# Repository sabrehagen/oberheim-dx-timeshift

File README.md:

# DX TimeShift: a snare delay knob for the Oberheim DX

DX TimeShift adds one new knob to the rear panel of an Oberheim DX drum machine (1983), next to
the existing SNARE tuning pot. The knob makes the snare drum play later than the sequencer asks,
by anything from nothing at all up to one whole beat. This lets you "lay the snare back" behind the
groove. The delay is measured in beats, not milliseconds, so it stays musically the same when you
change the tempo. With the knob turned fully down the DX behaves exactly as it did from the factory.
The mod is a small plug-in circuit board. It sits in the socket of one chip on the DX main board
(U701), so it can be removed again. The only permanent change is one hole in the rear panel.

*The assembled DX TimeShift rev A board (3D render from the KiCad design). The 16-way box header
J1 DX PLUG is at the back right, the Arduino Nano at the front left, and the socket U1 for the
DX's own U701 chip is between them.*

> **Status: Design complete; NOT yet bench-verified on a real DX.**
>
> The circuit, the circuit board, the firmware and the drawings are finished and checked against
> each other. Nobody has yet fitted a TimeShift board to a real DX. Several facts about the DX were
> worked out from schematics, photos and the original firmware, and still need one measurement on
> the bench. The most important open questions are:
>
> 1. **Q0:** Is your unit a plain DX (main board 1721A)? The board does NOT fit a DXa (board 1906).
>    **Owner's answer (2026-11-06): yes, it is a plain Oberheim DX.** The technician still reads the
>    board title and the ROM labels when the lid is open, to record the board number and firmware version.
> 2. **Q1:** Is U701 in a socket? If it is soldered in, the mod is no longer fully reversible.
>    **Owner's note:** the voice chips on this unit were socketed after purchase. U701 is a logic chip,
>    not a voice chip, so the technician still checks it with a torch (one minute).
> 3. **Q2:** What do the snare trigger lines (RST2, FFA2, FFB2) really look like on a logic analyser?
> 4. **Q3:** Is there enough height under the closed lid for the board (about 32 mm)?
> 5. **Q4:** Does the U701 clock line (GEN0*) stay clean when it runs through the ribbon cable?
> 6. **Q5:** Does the CLOCK OUT tap at R791 behave as expected, and does it keep ticking when the sequencer is stopped?
> 7. **Q6:** Is there room behind the rear panel for the new pot?
> 8. **Q7:** Does the DX +5 V supply stay healthy with the board running?
> 9. **Ribbon mapping:** every one of the 16 conductors must pass a continuity check before first power-up.
>
> Each question, with the exact measurement that answers it, is in
> [docs/05-bench-verification.md](docs/05-bench-verification.md).

## Who this is for

* **The owner** of an Oberheim DX who wants a "laid back" snare. Read
  [docs/00-start-here.md](docs/00-start-here.md). It explains what the mod does, what it costs and
  how it will behave.
* **The electronics technician** who builds and fits it. You need to be comfortable with
  through-hole soldering, a multimeter, and working inside mains-powered vintage equipment. An
  oscilloscope or a logic analyser is needed for the verification steps. No surface-mount
  soldering is needed.
* **Anyone curious** about how a 1983 drum machine triggers its sounds. Read
  [docs/01-theory-of-operation.md](docs/01-theory-of-operation.md).

## If you are the technician, read in this order

| Step | Document | What you get from it |
|---|---|---|
| 1 | [docs/00-start-here.md](docs/00-start-here.md) | The big picture, the model check, the shopping list, the order of work |
| 2 | [docs/05-bench-verification.md](docs/05-bench-verification.md) | The open questions. Answer Q0, Q1, Q3 and Q6 before you order anything. |
| 3 | [docs/01-theory-of-operation.md](docs/01-theory-of-operation.md) | How the DX triggers the snare and how the TimeShift board delays it |
| 4 | [docs/bom.md](docs/bom.md) | Parts, part numbers, prices and tools |
| 5 | [docs/02-build-the-board.md](docs/02-build-the-board.md) | Ordering the PCB, soldering, making the ribbon cable, continuity check, flashing, bench test |
| 6 | [docs/03-install-in-the-dx.md](docs/03-install-in-the-dx.md) | Fitting the board, drilling the panel, the pot and clock wiring |
| 7 | [docs/04-test-and-calibrate.md](docs/04-test-and-calibrate.md) | First power-on, measurements, troubleshooting, how to remove the mod |
| Reference | [hardware/README.md](hardware/README.md) | The complete pin and net table. This is the reference for every pin number. |
| Reference | [firmware/README.md](firmware/README.md) | Flashing the Nano, settings, the serial status line |
| Reference | [hardware/mechanical/README.md](hardware/mechanical/README.md) | Drill template, wiring diagram, continuity sheet |

## Option B: a delayed snare EPROM (idea recorded, not yet documented)

A lighter alternative that needs no new circuit board: burn a copy of the snare sample EPROM
(U206, a socketed 2764) with a block of silence in front, so the snare plays late by a fixed
number of milliseconds. The tuning pot keeps working (the lag shrinks slightly when the snare is
tuned up). Limits: the lag is fixed, not tempo-locked, and the chip has room for roughly 20 to
60 ms of lead-in before the snare tail is cut (about 200 ms if the SJ2/SJ3 solder jumpers are
moved). A 27C256 on a small adapter with a two-pole switch could offer four selectable lags.
The script, procedure and adapter drawing for this option have not been written yet.
**To resume this work, start from [docs/NEXT-STEPS.md](docs/NEXT-STEPS.md), which holds the full brief.**

## Interactive 3D walkthrough

There is an interactive 3D walkthrough of the DX, the board, the build and the installation.
It is live at
**<https://jacksondelahunt.com/oberheim-dx-timeshift/>** (also reachable as
<https://sabrehagen.github.io/oberheim-dx-timeshift/>). It plays at 2x by default. The DX is drawn by a
procedural model built from the reference photos (v2, no third-party assets). The earlier simple
stylised model is still available with the **DX model** button in the header or by adding
`?dx=v1` to the address. To run it on your own computer, see
[webapp/README.md](webapp/README.md).

*The web walkthrough. Each stage has a 3D view with labels on the real parts and a side panel
with the text. Items that are TO BE CONFIRMED are marked in amber.*

## Repository map

| Folder or file | What is in it |
|---|---|
| `README.md` | This page |
| `PROJECT_BRIEF.md` | The design brief: the single source of truth for the design decisions (sections 3 to 3.6) |
| `docs/` | The step-by-step guides (00 to 05), the bill of materials, the research findings and the collected reference documents |
| `hardware/` | The KiCad 9 design, Gerber files for ordering the PCB, schematic PDF, 3D renders and the mechanical drawings |
| `firmware/` | The Arduino Nano program, its settings file and PC tests |
| `webapp/` | The interactive 3D walkthrough (Vite and three.js) |
| `.github/` | The workflow that publishes the walkthrough to GitHub Pages |

## Safety notes

* **Mains voltage.** The DX has a mains transformer, fuse and line filter inside the case. Always
  switch off and **unplug the mains cable** before you open the lid or touch anything inside.
* **Stored energy.** The DX power supply has a 10 000 µF capacitor (C723). Wait at least a minute
  after unplugging before you work inside.
* **Static.** U701 is a 1983 CMOS chip (Motorola MC14174B). Wear an anti-static wrist strap
  connected to the DX chassis while you handle it. It cannot be bought new in the same form.
* **The memory battery.** The DX keeps your patterns in battery-backed memory. Never connect
  anything to the battery-backed "+5M" rail. Do not remove the battery or the memory chips. Save
  your patterns to cassette before you start, as the warning printed on the DX board advises.
* **USB.** The Nano's 5 V pin is connected to the DX logic supply. **Unplug the Nano before you
  connect USB**, or connect USB only while the DX is switched ON. Never plug USB into the Nano
  while it sits in an installed board in a switched-off DX.
* **Do not force anything.** Old sockets and chip legs bend easily. If a part does not go in,
  stop and look.

## Licence and credits

* The project's own original work is licensed as set out in [LICENSE.md](LICENSE.md): the
  hardware design under **CERN-OHL-P v2**, and the firmware, web app and documentation under
  **MIT**. The owner may change this later.
* The documents, schematics, manuals and photos in `docs/reference/` belong to their owners
  (Oberheim Electronics or its successors, Electrongate, the E&MM publisher, and the Wikimedia
  Commons photographers under their stated licences). They are kept here for repair and
  modification research only. See [docs/reference/INDEX.md](docs/reference/INDEX.md) for each
  source and its copyright notice.
* The research behind every pin number and timing value is in
  [docs/research/dx-findings.md](docs/research/dx-findings.md), with citations.

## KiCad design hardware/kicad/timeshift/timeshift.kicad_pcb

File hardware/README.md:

# DX TimeShift rev A: hardware

This folder holds the complete KiCad 9 design of the DX TimeShift board (snare delay
interposer for the Oberheim DX, board 1721A, socket U701). It also holds every file made
from that design. The circuit is exactly PROJECT_BRIEF.md section 3.5 (LOCKED). The signal
facts behind it are in `docs/research/dx-findings.md` sections b, c, d and h.

> **Fits Oberheim DX board 1721A (U701). NOT for the DXa (board 1906, U715).**
> **UNPLUG NANO BEFORE USB.** The Nano's 5 V pin is wired to the DX logic rail. Flash the Nano
> while it is OUT of the board, or only while the DX is switched on.

## 1. What each file is

| Path | What it is |
|---|---|
| `kicad/timeshift/timeshift.kicad_pro` | KiCad 9 project. Open this file in KiCad. |
| `kicad/timeshift/timeshift.kicad_sch` | Schematic, one A3 sheet in blocks A to F. Every library symbol is embedded. |
| `kicad/timeshift/timeshift.kicad_pcb` | PCB: 2 layers, fully routed, GND pours on both layers |
| `kicad/timeshift/timeshift.kicad_sym`, `sym-lib-table` | Project symbol library. It has one symbol, J1 `DX_PLUG_2x08`. |
| `kicad/timeshift/timeshift.pretty/Arduino_Nano_Socketed.kicad_mod`, `fp-lib-table` | Project footprint: `Module:Arduino_Nano` with identical pads, plus 3D models of the Nano and its two 1x15 female headers |
| `kicad/timeshift/3d/Arduino_Nano_v3_on_sockets.step` | Simple colour 3D model of a Nano v3 on sockets. The KiCad library has no Nano model. |
| `kicad/timeshift/reports/erc.rpt` | ERC report: **0 errors, 0 warnings** (all severities) |
| `kicad/timeshift/reports/drc.rpt` | DRC report, including schematic parity: **0 violations, 0 unconnected, 0 parity issues** (all severities) |
| `kicad/timeshift/reports/timeshift.net` | Netlist exported from the schematic. The PCB is built from it. |
| `kicad/tools/` | Generator scripts. The whole design is rebuilt from `netlist.py` (section 3). |
| `kicad/3dmodels-cache/` | The KiCad 9 library 3D models this board uses (3.7 MB). **Committed to the repo**, so renders, GLB and STEP rebuild offline. `fetch_3dmodels.sh` re-downloads any that are missing. |
| `exports/schematic.pdf`, `exports/schematic.svg` | Schematic for printing or viewing |
| `exports/pcb-top.svg`, `exports/pcb-bottom.svg` | Copper + mask + silkscreen + outline, top and bottom (the bottom view is mirrored) |
| `exports/fab-assembly-top.pdf` | Fab/assembly drawing: F.Fab + F.Silkscreen + Edge.Cuts with title block |
| `exports/board.glb` | 3D model with tracks, pads, zones, silkscreen, soldermask and component models. It is used by the web app. |
| `exports/board.step` | 3D STEP of the assembled board, for mechanical CAD |
| `exports/bom.csv` | BOM exported from the schematic, grouped by value and footprint, with part numbers. The J1 cable row names the DIP-16 IDC plug as **Adam Tech FDP-316-T** (alternative HARTING 09181169622), the same part as `docs/bom.csv`. |
| `exports/positions.csv` | Component positions (mm, KiCad coordinates, top side) |
| `gerbers/timeshift-revA-gerbers.zip` | **Upload this to JLCPCB/PCBWay.** See `gerbers/README.md` for order settings. |
| `renders/top.png`, `bottom.png`, `perspective.png`, `perspective-2.png` | 3D renders, 2384 x 1680 px, high quality |
| `renders/top-bare-board.png` | Top render without parts, so all the silkscreen is visible |
| `renders/assembly-diagram.svg` / `.png` | **Labelled top view for assembly.** Every connector, IC and test point has a callout. |

## 2. The board at a glance

* 84.0 x 63.0 mm, 2 layers, FR-4 1.6 mm, all parts through-hole, 4 x M3 (3.2 mm) mounting
  holes 3.5 mm in from each corner (hole centres 77.0 x 56.0 mm apart).
* Tracks are 0.5 mm for signals and 0.8 mm for +5V. Clearance is 0.2 mm. Vias are 1.0/0.5 mm.
  Copper is kept 0.5 mm from the board edge.
* GND is carried by a copper pour on the **bottom** (the main plane, as the brief asks). A
  second GND pour on the top joins the bottom islands that the tracks cut off. Every GND pad
  has at least two thermal spokes or a solid connection.
* Layout (top view): J1 "DX PLUG" is top centre, with U1 (socket for the original U701)
  directly below it. U3 (74HC157) is on the left and the 1 k resistors R1 to R3 sit between
  U3 and U1. The Nano is across the bottom with its USB end on the LEFT. U4 (74HC14) is
  bottom right. **All three DIP sockets (U1, U3, U4) have their notch / pin 1 at the LEFT
  end.** J3 "CLK" and J2 "POT" are on the right edge. The PPQN jumper JP1 is at the left
  edge. Test points TP2/TP3/TP4 are next to J1, TP1 is at the left edge and TP5 is next to
  U4.
* Decoupling sits at the pins it serves. C2 is about 3 mm from U1 pin 16 and C3 about 6 mm
  from U3 pin 16. C4's +5V pad is 4.0 mm from U4 pin 14 (VCC). C5 is just below the Nano:
  its +5V pad is 3.2 mm from Nano pin 27 (+5V) and its GND pad 3.2 mm from pin 29 (GND).

## 3. How to open and how to regenerate

**Open:** install KiCad 9 and open `kicad/timeshift/timeshift.kicad_pro`. The project
libraries (`timeshift.kicad_sym`, `timeshift.pretty`) are found through `${KIPRJMOD}`. All
other symbols and footprints come from the standard KiCad 9 libraries.

**Regenerate everything** with Docker. This rebuilds the libraries, schematic, ERC, netlist
check, PCB, autorouting, pours, DRC, all exports, Gerbers, renders and the diagram:

```sh
docker pull kicad/kicad:9.0
docker pull ghcr.io/freerouting/freerouting:latest
hardware/kicad/tools/build_all.sh            # about 8 minutes, mostly the 3D renders
```

The 3D models come from the committed `hardware/kicad/3dmodels-cache/` (3.7 MB).
`build_all.sh` only downloads models that are missing there, so the build needs no network
access for them. It does need the two Docker images.

If Docker cannot bind-mount your checkout (for example, you are working inside a container),
start a helper container once and use copy mode. Copy mode only syncs `hardware/kicad`,
`exports`, `gerbers` and `renders`:

```sh
docker run -d --name kicadws kicad/kicad:9.0 sleep infinity
KX_MODE=copy hardware/kicad/tools/build_all.sh
```

Single steps, run from the repository root (this is what `tools/kx.sh` does):

```sh
K='docker run --rm --user '"$(id -u):$(id -g)"' -e HOME=/tmp -e KICAD9_3DMODEL_DIR=/work/hardware/kicad/3dmodels-cache -v '"$PWD"':/work -w /work kicad/kicad:9.0'
$K kicad-cli sch erc --severity-all -o hardware/kicad/timeshift/reports/erc.rpt hardware/kicad/timeshift/timeshift.kicad_sch
$K kicad-cli pcb drc --schematic-parity --severity-all -o hardware/kicad/timeshift/reports/drc.rpt hardware/kicad/timeshift/timeshift.kicad_pcb
$K kicad-cli sch export pdf -o hardware/exports/schematic.pdf hardware/kicad/timeshift/timeshift.kicad_sch
$K kicad-cli pcb export glb -f --subst-models --include-tracks --include-pads --include-zones --include-silkscreen --include-soldermask -o hardware/exports/board.glb hardware/kicad/timeshift/timeshift.kicad_pcb
$K kicad-cli pcb render --quality high --side top -w 2400 -h 1700 -o hardware/renders/top.png hardware/kicad/timeshift/timeshift.kicad_pcb
$K python3 hardware/kicad/tools/gen_pcb.py      # pcbnew Python API is available in the image
```

### The generator scripts (`kicad/tools/`)

| Script | Job |
|---|---|
| `netlist.py` | **Single source of truth:** every part, value, footprint, part number and pin-to-net assignment (= brief 3.5). The header-to-DIP mapping `HDR2DIP` is here. |
| `gen_libs.py` | Writes the J1 symbol (pin number = header pin, pin name = DIP pin), the socketed Nano footprint and the lib tables |
| `gen_project.py` | Writes `timeshift.kicad_pro`: net classes (Default 0.5 mm, Power 0.8 mm) and design rules |
| `gen_schematic.py` | Draws the schematic from `netlist.py`, using KiCad standard symbols embedded in the file |
| `check_netlist.py` | Compares the netlist KiCad exports from the schematic with `netlist.py`, net by net. The build stops on any difference. |
| `gen_pcb.py` + `silk.py` | Places the footprints and assigns nets from the exported netlist, so the PCB links to the schematic like "Update PCB from Schematic". Then it adds the outline and silkscreen and writes the Specctra DSN. |
| `route.sh` | Autoroutes with Freerouting in Docker. Neck-down is off, so every track keeps its class width. Freerouting is not fully deterministic, so the script retries (up to 5 runs) until 0 connections are unrouted. |
| `finish_pcb.py` | Imports the routes and adds and fills the GND pours. It gives a pad a solid zone connection where only one thermal spoke would fit. |
| `exports.sh` | All `kicad-cli` exports, Gerbers + drill files + zip, and 3D renders |
| `gen_diagram.py` | Draws the labelled assembly diagram from the real board data |
| `make_nano_3d.py` | Builds the Nano 3D model with CadQuery. It runs on the host and is optional, because the STEP file is committed. |
| `fetch_3dmodels.sh` | Downloads the KiCad 9 library 3D models this board uses (the Docker image ships without them) |
| `preview.py`, `bare_board.py` | Debug preview SVG and a model-less copy of the board for the bare-board render |

## 4. Design decisions

1. **Netlist first.** `netlist.py` is written straight from brief 3.5. The schematic is drawn
   from it, and KiCad's exported netlist must match it exactly (`check_netlist.py`). The PCB
   then takes its nets from that exported netlist, and DRC schematic parity confirms the PCB
   matches the schematic. So the brief, the schematic and the PCB cannot drift apart.
2. **J1 uses DIP pin numbers.** J1's symbol pin *numbers* are the box-header pins, which are
   also the ribbon conductors. Its pin *names* are `DIP1`...`DIP16`, the DIP-16 plug pin each
   header pin lands on. The symbol is drawn in DIP order, so it reads like U701. Net names say
   which U701 pin they carry (`U701_9_~{GEN0}`, `RST2_PLUG` = DIP 15, ...). The silkscreen
   also prints the DIP pin number next to every header pin ("DIP 16 15 ... 9" above,
   "DIP 1 2 ... 8" below).
3. **Interception is complete.** U1 pins 10/12/15 go only to the 74HC157 A inputs and,
   through R1 to R3 (1 k), to the Nano. J1 DIP 10/12/15 are driven only by the 74HC157 Y
   outputs. The other 13 pins go straight from J1 to U1 on the same DIP number.
4. **Fail-safe bypass.** R5 (10 k) pulls the mux select low, which selects the A inputs
   (bypass). A missing, blank, crashed or resetting Nano therefore leaves the DX stock.
5. **Clock input.** J3 pin 1 feeds R6 (10 k series). The node has R7 (100 k) to GND and C7
   (1 nF) to GND, then goes through two 74HC14 inverters in series to CLK_IN (D3). The
   output is non-inverting, so a rising edge at R791 is a rising edge at D3. The four unused
   74HC14 inputs are tied to GND.
6. **Power** comes only from J1 (DIP16 = +5 V, DIP8 = GND). C1 (10 µF) is next to J1, and
   there is a 100 nF cap at the supply pins of each of U1 (C2), U3 (C3), U4 (C4, 4 mm from
   pin 14) and the Nano (C5, 3 mm from pins 27/29). The board has no ±12 V.
7. **Removable parts.** Every IC is socketed. The Nano plugs into two 1x15 female headers.
   U1 is only a socket: it holds the original U701 chip taken out of the DX. Its notch is
   marked "NOTCH = PIN 1 END" with an arrow, and silk text reads
   "U1 = ORIGINAL U701 (MC14174B)". U1, U3 and U4 all face the same way, with the notch at the
   left end, so no chip is the odd one out. A chip fitted backwards swaps pins 7/8 and 14/16
   and reverse-powers itself.
8. **Autorouting.** Freerouting routes the signal and +5V nets at the full 0.5/0.8 mm widths
   (neck-down off). The GND pours carry GND. The board was enlarged to 84 x 63 mm so that
   everything routes at those widths (see section 7).

## 5. Design review against PROJECT_BRIEF.md 3.5 (LOCKED)

| # | LOCKED requirement (brief 3.5) | How the design meets it |
|---|---|---|
| 1 | Nano D2 (INT0) = RST2_IN from U701 pin 15 | U1.15 `RST2_CHIP` → R1 1 k → `RST2_IN` → U2 pin 5 (D2) |
| 2 | D3 (INT1) = CLK_IN after the Schmitt buffer | U4 pin 4 (2nd gate) → `CLK_IN` → U2 pin 6 (D3), TP5 |
| 3 | D4 = FFA2_IN from U701 pin 12 | U1.12 `FFA2_CHIP` → R2 1 k → `FFA2_IN` → U2 pin 7 (D4) |
| 4 | D5 = FFB2_IN from U701 pin 10 | U1.10 `FFB2_CHIP` → R3 1 k → `FFB2_IN` → U2 pin 8 (D5) |
| 5 | D6 = RST2_OUT → 74HC157 1B | U2 pin 9 (D6) → U3 pin 3 (1B) |
| 6 | D7 = FFA2_OUT → 2B | U2 pin 10 (D7) → U3 pin 6 (2B) |
| 7 | D8 = FFB2_OUT → 3B | U2 pin 11 (D8) → U3 pin 10 (3B) |
| 8 | D9 = MUX_SEL → U3 pin 1 (S), 10 k pull-down = bypass | U2 pin 12 (D9) → U3 pin 1, R5 10 k to GND |
| 9 | D10/D11 = PPQN_J1/J2, jumper to GND (internal pull-ups) | U2 pin 13 (D10) → JP1 pin 1 and U2 pin 14 (D11) → JP1 pin 3. JP1 pins 2/4 = GND. The positions are called **"JP1 1-2"** (D10, closed = 48 PPQN) and **"JP1 3-4"** (D11, closed = 24 PPQN); both open = 96. The silkscreen says "PPQN / open=96 / JP1 1-2=48 / JP1 3-4=24". J1 and J2 are connectors, never jumper names. |
| 10 | D12 = TP_REPLAY test point | U2 pin 15 (D12) → TP1 "REPLAY" |
| 11 | D13 = LED_ACT on-board LED | The Nano's own "L" LED. Nothing external is needed, so U2 pin 16 has a no-connect flag and a note in the schematic. |
| 12 | A0 = POT_W via 1 k series + 100 nF to GND | J2.2 → R4 1 k → `POT_W` → U2 pin 19 (A0). C6 100 nF from `POT_W` to GND. |
| 13 | 74HC157 /E (pin 15) = GND | U3.15 = GND |
| 14 | ch1: 1A = RST2 chip, 1B = RST2_OUT, 1Y → plug pin 15 | U3.2 = `RST2_CHIP`, U3.3 = `RST2_OUT`, U3.4 → `RST2_PLUG` → J1 header pin 4 = DIP 15, TP3 |
| 15 | ch2: 2A = FFA2 chip, 2B = FFA2_OUT, 2Y → plug pin 12 | U3.5, U3.6, U3.7 → `FFA2_PLUG` → J1 header pin 10 = DIP 12 |
| 16 | ch3: 3A = FFB2 chip, 3B = FFB2_OUT, 3Y → plug pin 10 | U3.11, U3.10, U3.9 → `FFB2_PLUG` → J1 header pin 14 = DIP 10 |
| 17 | ch4 unused: 4A, 4B to GND, 4Y n/c | U3.14, U3.13 = GND. U3.12 has a no-connect flag. |
| 18 | 74HC14: J_CLK.1 → 10 k → node (100 k + 1 nF to GND) → gate 1 → gate 2 → CLK_IN, unused inputs GND | J3.1 → R6 10 k → `CLK_RC` (R7 100 k, C7 1 nF) → U4.1 → U4.2/U4.3 → U4.4 = `CLK_IN`. U4 pins 5, 9, 11, 13 = GND. Outputs 6, 8, 10, 12 are not connected. |
| 19 | U1 = DIP-16 socket for the original U701 | `Package_DIP:DIP-16_W7.62mm_Socket`, value "MC14174B (orig. U701)" |
| 20 | U1 pins 1–9, 11, 13, 14, 16 straight to the same J1 DIP pin | 13 nets `U701_n_...`/`+5V`/`GND`. Each joins U1 pin n to the J1 header pin that lands on DIP n (table in section 6). Proven by `check_netlist.py` + DRC parity. |
| 21 | U1 pins 10/12/15 only to the Nano inputs (via 1 k) and the mux A inputs | `*_CHIP` nets hold only U1, U3 A input, R1/R2/R3 (and TP2 on RST2). They have no connection to J1. |
| 22 | J1 pins 10/12/15 driven only by the mux Y outputs | `*_PLUG` nets hold only U3 Y, J1 (and TP3 on RST2) |
| 23 | J1 = 2x8 shrouded box header, pin 1 marked | `Connector_IDC:IDC-Header_2x08_P2.54mm_Vertical`. Pin 1 has a square pad and a ▲ silk mark. Label "DX PLUG". |
| 24 | Standard DIP IDC mapping, and J1 schematic nets already use DIP pin numbers | J1 pin names are DIP1...DIP16 per the mapping. Net names carry the U701 pin. Silk prints the DIP number at every header pin. The mapping is also printed on the back silkscreen. |
| 25 | J2 "POT" JST-XH 3: 1 GND (CCW), 2 wiper, 3 +5 V (CW) | `JST_XH_B3B-XH-A_1x03_P2.50mm_Vertical`. Silk "J2 POT 1 GND 2 WIPER 3 +5V". |
| 26 | J3 "CLK" JST-XH 2: 1 CLK (R791 lead), 2 GND | `JST_XH_B2B-XH-A_1x02_P2.50mm_Vertical`. Silk "J3 CLK 1 R791 2 GND". |
| 27 | JP1 2x2 header for PPQN_J1/J2 to GND | `PinHeader_2x02_P2.54mm_Vertical`, with the silk legend "PPQN / open=96 / JP1 1-2=48 / JP1 3-4=24" |
| 28 | TP1 = TP_REPLAY, TP2 = RST2 chip, TP3 = RST2 plug, TP4 = GND, TP5 = CLK_IN | Exactly these, as Keystone 5005 compact loops, each named on the silkscreen |
| 29 | C_bulk 10 µF at J1; 100 nF next to U1, U3, U4 and the Nano | C1 10 µF beside J1. C2 is 3 mm from U1 pin 16 and C3 6 mm from U3 pin 16. C4's +5V pad is 4.0 mm from U4 pin 14. C5 is right below the Nano, 3.2 mm from pin 27 (+5V) and 3.2 mm from pin 29 (GND). |
| 30 | Power only from U701 pins 16/8 via the plug, no ±12 V | +5V and GND enter only through J1 header pins 2 (DIP16) and 15 (DIP8) |
| 31 | 2 layers, about 65 x 40 mm, 4 x M3 at the corners, all through-hole | 2 layers, all THT, 4 x M3 at the corners. **Size is 84 x 63 mm**, see section 7. |
| 32 | Silk: "DX TIMESHIFT rev A — SNARE — fits Oberheim DX board 1721A (U701). NOT for DXa (U715)" | Two lines along the bottom edge: "DX TIMESHIFT rev A — SNARE" / "fits Oberheim DX board 1721A (U701). NOT for DXa (U715)". The back silkscreen repeats the model warning. |
| 33 | Nano on two 1x15 female headers, removable | Footprint `timeshift:Arduino_Nano_Socketed` (pads identical to `Module:Arduino_Nano`). The BOM lists the sockets. |
| 34 | "UNPLUG NANO BEFORE USB" next to the Nano | Printed in bold at the Nano's USB end, which is the left board edge |

## 6. Ribbon / DIP plug mapping and the as-built pin/net table

A 16-way ribbon goes from J1 to a DIP-16 IDC plug in the DX's U701 socket. Ribbon conductor
*n* lands on header pin *n*. **J1's pin labels (schematic pin names and PCB silkscreen numbers)
already use the DIP pin numbers after this mapping.**

**TO BE CONFIRMED on the bench (a mandatory step before first power-up):** with the cable made
up and nothing plugged in, use a continuity meter to check every pair in the table below.
Check DIP 16 = +5 V and DIP 8 = GND above all.

| J1 header pin = ribbon conductor | DIP plug pin = U701 socket pin | Net on the TimeShift board | U701 / DX signal (findings b1) | U1 pin on the board |
|---|---|---|---|---|
| 1 | 1 | `U701_1_~{CLR}` | CLR, tied to +5 V in the DX | 1 (same net) |
| 2 | 16 | `+5V` | VDD +5 V (supplies the board) | 16 (same net) |
| 3 | 2 | `U701_2_RST1` | Q1 = RST1 (bass) | 2 (same net) |
| 4 | 15 | `RST2_PLUG` (mux 1Y) | Q6 = RST2 (snare), **intercepted** | 15 = `RST2_CHIP` |
| 5 | 3 | `U701_3_BUS_D0` | D1 input = data bus D0 | 3 (same net) |
| 6 | 14 | `U701_14_BUS_D3` | D6 input = data bus D3 | 14 (same net) |
| 7 | 4 | `U701_4_BUS_D1` | D2 input = data bus D1 | 4 (same net) |
| 8 | 13 | `U701_13_BUS_D4` | D5 input = data bus D4 | 13 (same net) |
| 9 | 5 | `U701_5_FFA1` | Q2 = FFA1 (bass) | 5 (same net) |
| 10 | 12 | `FFA2_PLUG` (mux 2Y) | Q5 = FFA2 (snare), **intercepted** | 12 = `FFA2_CHIP` |
| 11 | 6 | `U701_6_BUS_D2` | D3 input = data bus D2 | 6 (same net) |
| 12 | 11 | `U701_11_BUS_D5` | D4 input = data bus D5 | 11 (same net) |
| 13 | 7 | `U701_7_FFB1` | Q3 = FFB1 (bass) | 7 (same net) |
| 14 | 10 | `FFB2_PLUG` (mux 3Y) | Q4 = FFB2 (snare), **intercepted** | 10 = `FFB2_CHIP` |
| 15 | 8 | `GND` | VSS (board ground) | 8 (same net) |
| 16 | 9 | `U701_9_~{GEN0}` | CLK = GEN0* write strobe | 9 (same net) |

Every net on the board as built (in KiCad, local nets carry a leading `/`):

| Net | Members (ref.pin, Nano pin name) |
|---|---|
| `+5V` | U1.16, U2.27 (+5V), U3.16, U4.14, J1.2, J2.3, C1.1, C2.1, C3.1, C4.1, C5.1 |
| `GND` | U1.8, U2.4, U2.29, U3.8, U3.13, U3.14, U3.15, U4.5, U4.7, U4.9, U4.11, U4.13, J1.15, J2.1, J3.2, JP1.2, JP1.4, R5.2, R7.2, C1.2, C2.2, C3.2, C4.2, C5.2, C6.2, C7.2, TP4.1 |
| `RST2_CHIP` | U1.15, U3.2 (1A), R1.1, TP2.1 |
| `RST2_IN` | U2.5 (D2), R1.2 |
| `RST2_OUT` | U2.9 (D6), U3.3 (1B) |
| `RST2_PLUG` | U3.4 (1Y), J1.4 (DIP15), TP3.1 |
| `FFA2_CHIP` | U1.12, U3.5 (2A), R2.1 |
| `FFA2_IN` | U2.7 (D4), R2.2 |
| `FFA2_OUT` | U2.10 (D7), U3.6 (2B) |
| `FFA2_PLUG` | U3.7 (2Y), J1.10 (DIP12) |
| `FFB2_CHIP` | U1.10, U3.11 (3A), R3.1 |
| `FFB2_IN` | U2.8 (D5), R3.2 |
| `FFB2_OUT` | U2.11 (D8), U3.10 (3B) |
| `FFB2_PLUG` | U3.9 (3Y), J1.14 (DIP10) |
| `MUX_SEL` | U2.12 (D9), U3.1 (S), R5.1 |
| `PPQN_J1` | U2.13 (D10), JP1.1 |
| `PPQN_J2` | U2.14 (D11), JP1.3 |
| `TP_REPLAY` | U2.15 (D12), TP1.1 |
| `POT_WIPER` | J2.2, R4.1 |
| `POT_W` | U2.19 (A0), R4.2, C6.1 |
| `CLK_TAP` | J3.1, R6.1 |
| `CLK_RC` | R6.2, R7.1, C7.1, U4.1 |
| `CLK_INV` | U4.2, U4.3 |
| `CLK_IN` | U4.4, U2.6 (D3), TP5.1 |
| `U701_1_~{CLR}` | U1.1, J1.1 |
| `U701_2_RST1` | U1.2, J1.3 |
| `U701_3_BUS_D0` | U1.3, J1.5 |
| `U701_4_BUS_D1` | U1.4, J1.7 |
| `U701_5_FFA1` | U1.5, J1.9 |
| `U701_6_BUS_D2` | U1.6, J1.11 |
| `U701_7_FFB1` | U1.7, J1.13 |
| `U701_9_~{GEN0}` | U1.9, J1.16 |
| `U701_11_BUS_D5` | U1.11, J1.12 |
| `U701_13_BUS_D4` | U1.13, J1.8 |
| `U701_14_BUS_D3` | U1.14, J1.6 |
| not connected (no-connect flag) | U2: D0, D1, both RESET, 3V3, AREF, A1–A7, D13 (= on-board LED), VIN. U3.12 (4Y). U4 outputs 6, 8, 10, 12. |

## 7. Check results, warnings and deviations from the brief

* **ERC** (`kicad-cli sch erc --severity-all`): 0 errors, 0 warnings, nothing excluded. Only
  GND has a PWR_FLAG. +5V is already driven by the Nano symbol's `+5V` pin, which is a power
  output, and a PWR_FLAG there would clash with it. In the real circuit +5 V comes from the DX
  through J1 DIP16.
* **DRC** (`kicad-cli pcb drc --schematic-parity --severity-all`): 0 violations, 0 unconnected
  items, 0 schematic-parity issues, nothing excluded. That includes silkscreen overlap,
  silkscreen on pads, edge clearance and text size.
* **Deviation: board size.** The board is 84 x 63 mm instead of about 65 x 40 mm. The parts
  alone cover about 2,600 mm²: the Nano with its 46 x 18 mm footprint, three DIP sockets, a
  29 mm long box header, seven 10 mm axial resistors, five test points and four corner holes.
  That is already the whole 65 x 40 area, before any routing. The brief allows growth if
  needed. The ribbon (10 to 15 cm) lets the board sit anywhere convenient inside the DX case.
* **Addition: a second GND pour on the top layer.** The brief asks for a GND pour on the
  bottom, and that is the main plane. A top pour was added because signal tracks on the
  bottom cut it into islands. Three GND pads (J1.15, C1.2, U2.4) have a solid zone connection
  instead of thermal spokes, because the pours can only reach them with one spoke. They need
  a little more heat when soldering.
* **Choices allowed by the brief:** the test points are Keystone 5005 compact loops (THT). The
  Nano footprint is a project copy of `Module:Arduino_Nano` with the same pads, plus 3D models
  of the Nano and its female headers. The U1 and U3 symbols are KiCad's `74LS174` and
  `74LS157`, which have the same pinout as MC14174B and 74HC157. The value fields carry the
  real part.
* **3D models.** The DIP sockets, box header, JST connectors, pin header, resistors,
  capacitors, test points and female headers use the official KiCad 9 models. The Nano model
  is a simplified one made for this project (board, ATmega, USB connector, LEDs, pins), with
  the right size and pin positions.
* **Still TO BE CONFIRMED on the bench** (from the brief and findings, not from this board):
  that U701 is socketed (findings Q1), the ribbon/IDC mapping (continuity check above), the
  RST2 pulse width (Q2), the CLOCK OUT tap at R791 (Q5), and the +5 V drop at U701 pin 16
  (Q7).

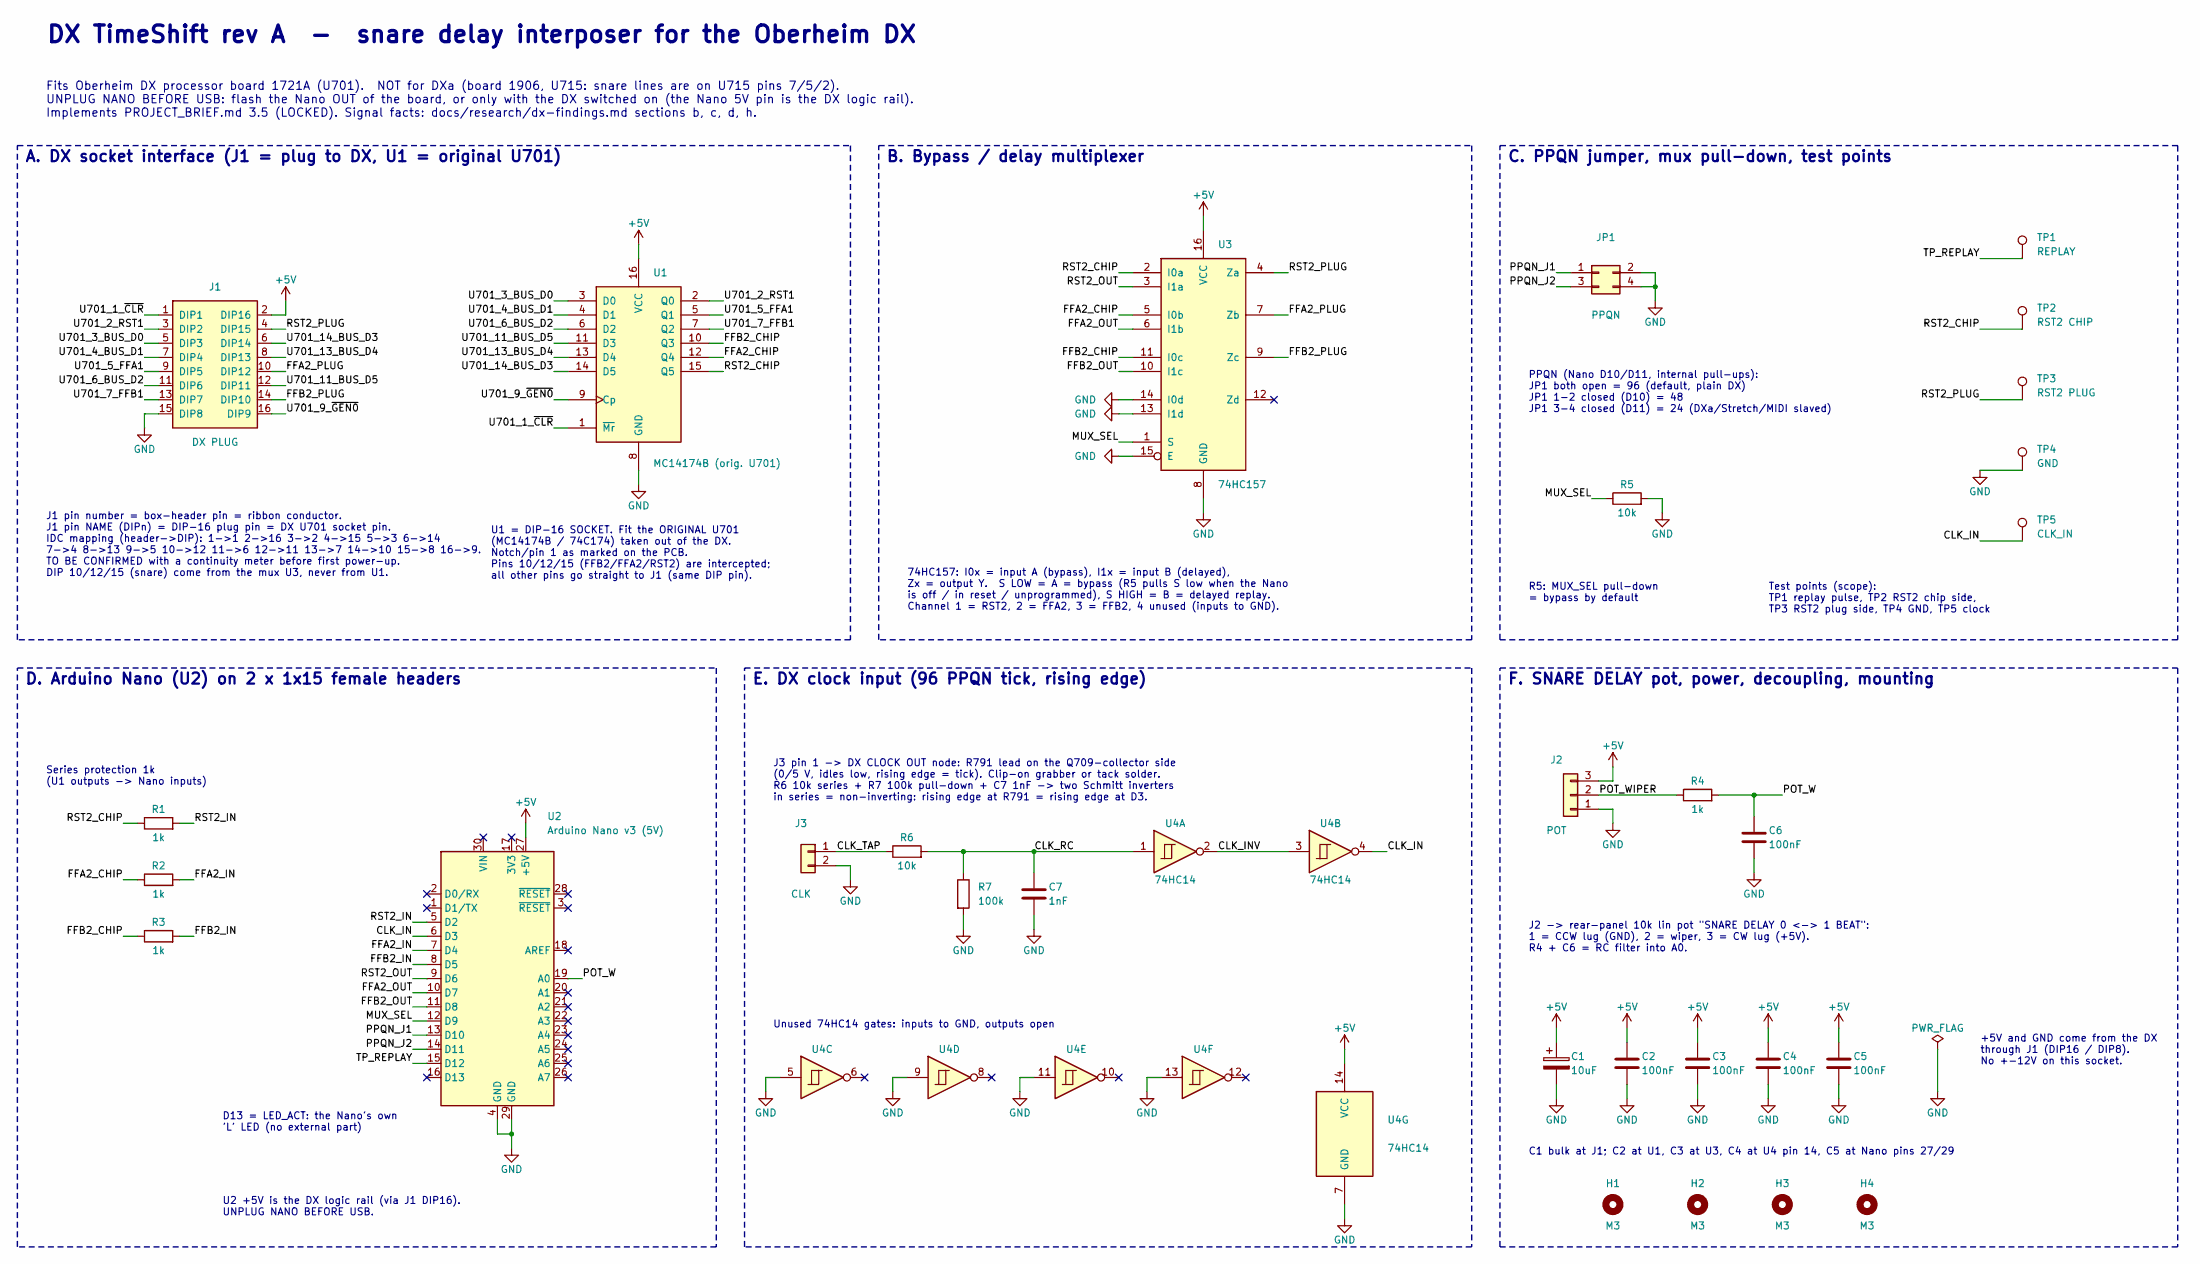
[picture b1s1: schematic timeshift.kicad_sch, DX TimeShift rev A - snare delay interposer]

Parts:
C1: 10uF; CP_Radial_D5.0mm_P2.00mm
C2, C3, C4, C5, C6: 100nF; C_Disc_D5.0mm_W2.5mm_P5.00mm
C7: 1nF; C_Disc_D5.0mm_W2.5mm_P5.00mm
H1, H2, H3, H4: M3; MountingHole_3.2mm_M3
J1: DX PLUG; IDC-Header_2x08_P2.54mm_Vertical; MPN 2x8 shrouded box header 2.54 mm, e.g. W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
J2: POT; JST_XH_B3B-XH-A_1x03_P2.50mm_Vertical; MPN JST B3B-XH-A (housing XHP-3, crimps SXH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
J3: CLK; JST_XH_B2B-XH-A_1x02_P2.50mm_Vertical; MPN JST B2B-XH-A (housing XHP-2, crimps SXH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
JP1: PPQN; PinHeader_2x02_P2.54mm_Vertical; MPN 2x2 pin header 2.54 mm + 1 jumper shunt
R1, R2, R3, R4: 1k; R_Axial_DIN0207_L6.3mm_D2.5mm_P10.16mm_Horizontal
R5, R6: 10k; R_Axial_DIN0207_L6.3mm_D2.5mm_P10.16mm_Horizontal
R7: 100k; R_Axial_DIN0207_L6.3mm_D2.5mm_P10.16mm_Horizontal
TP1: REPLAY; TestPoint_Keystone_5005-5009_Compact; MPN Keystone 5005 (red)
TP2: RST2 CHIP; TestPoint_Keystone_5005-5009_Compact; MPN Keystone 5005 (red)
TP3: RST2 PLUG; TestPoint_Keystone_5005-5009_Compact; MPN Keystone 5005 (red)
TP4: GND; TestPoint_Keystone_5005-5009_Compact; MPN Keystone 5006 (black)
TP5: CLK_IN; TestPoint_Keystone_5005-5009_Compact; MPN Keystone 5005 (red)
U1: MC14174B (orig. U701); DIP-16_W7.62mm_Socket; MPN DIP-16 IC socket, 7.62 mm (e.g. TE 1-21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
U2: Arduino Nano v3 (5V); Arduino_Nano_Socketed; MPN Arduino Nano v3 (A000005) or ATmega328P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
U3: 74HC157; DIP-16_W7.62mm_Socket; MPN 74HC157N (DIP-16), e.g. TI SN74HC157N
U4: 74HC14; DIP-14_W7.62mm_Socket; MPN 74HC14N (DIP-14), e.g. TI SN74HC14N

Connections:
+5V: C1.1, C2.1, C3.1, C4.1, C5.1, J1.2 (DIP16), J2.3, U1.16 (VCC), U2.27 (+5V), U3.16 (VCC), U4.14 (VCC)
/CLK_IN: TP5.1, U2.6 (D3), U4.4
/CLK_INV: U4.2, U4.3
/CLK_RC: C7.1, R6.2, R7.1, U4.1
/CLK_TAP: J3.1, R6.1
/FFA2_CHIP: R2.1, U1.12 (Q4), U3.5 (I0b)
/FFA2_IN: R2.2, U2.7 (D4)
/FFA2_OUT: U2.10 (D7), U3.6 (I1b)
/FFA2_PLUG: J1.10 (DIP12), U3.7 (Zb)
/FFB2_CHIP: R3.1, U1.10 (Q3), U3.11 (I0c)
/FFB2_IN: R3.2, U2.8 (D5)
/FFB2_OUT: U2.11 (D8), U3.10 (I1c)
/FFB2_PLUG: J1.14 (DIP10), U3.9 (Zc)
/MUX_SEL: R5.1, U2.12 (D9), U3.1 (S)
/POT_W: C6.1, R4.2, U2.19 (A0)
/POT_WIPER: J2.2, R4.1
/PPQN_J1: JP1.1, U2.13 (D10)
/PPQN_J2: JP1.3, U2.14 (D11)
/RST2_CHIP: R1.1, TP2.1, U1.15 (Q5), U3.2 (I0a)
/RST2_IN: R1.2, U2.5 (D2)
/RST2_OUT: U2.9 (D6), U3.3 (I1a)
/RST2_PLUG: J1.4 (DIP15), TP3.1, U3.4 (Za)
/TP_REPLAY: TP1.1, U2.15 (D12)
/U701_1_~CLR: J1.1 (DIP1), U1.1 (~Mr)
/U701_2_RST1: J1.3 (DIP2), U1.2 (Q0)
/U701_3_BUS_D0: J1.5 (DIP3), U1.3 (D0)
/U701_4_BUS_D1: J1.7 (DIP4), U1.4 (D1)
/U701_5_FFA1: J1.9 (DIP5), U1.5 (Q1)
/U701_6_BUS_D2: J1.11 (DIP6), U1.6 (D2)
/U701_7_FFB1: J1.13 (DIP7), U1.7 (Q2)
/U701_9_~GEN0: J1.16 (DIP9), U1.9 (Cp)
/U701_11_BUS_D5: J1.12 (DIP11), U1.11 (D3)
/U701_13_BUS_D4: J1.8 (DIP13), U1.13 (D4)
/U701_14_BUS_D3: J1.6 (DIP14), U1.14 (D5)
GND: C1.2, C2.2, C3.2, C4.2, C5.2, C6.2, C7.2, J1.15 (DIP8), J2.1, J3.2, JP1.2, JP1.4, R5.2, R7.2, TP4.1, U1.8 (GND), U2.4 (GND), U2.29 (GND), U3.8 (GND), U3.13 (I1d), U3.14 (I0d), U3.15 (E), U4.5, U4.7 (GND), U4.9, U4.11, U4.13

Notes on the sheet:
DX TimeShift rev A - snare delay interposer for the Oberheim DX
Fits Oberheim DX processor board 1721A (U701). NOT for DXa (board 1906, U715: snare lines are on U715 pins 7/5/2). UNPLUG NANO BEFORE USB: flash the Nano OUT of the board, or only with the DX switched on (the Nano 5V pin is the DX logic rail). Implements PROJECT_BRIEF.md 3.5 (LOCKED). Signal facts: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
A. DX socket interface (J1 = plug to DX, U1 = original U701)
J1 pin number = box-header pin = ribbon conductor. J1 pin NAME (DIPn) = DIP-16 plug pin = DX U701 socket pin. IDC mapping (header->DIP): 1->1 2->16 3->2 4->15 5->3 6->14 7->4 8->13 9->5 10->12 11->6 12->11 13->7 14->10 15->8 16->9. TO BE CONFIRMED with a continuity meter before first power-up. DIP 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
U1 = DIP-16 SOCKET. Fit the ORIGINAL U701 (MC14174B / 74C174) taken out of the DX. Notch/pin 1 as marked on the PCB. Pins 10/12/15 (FFB2/FFA2/RST2) are intercepted; all other pins go straight to J1 (same DIP pin).
B. Bypass / delay multiplexer
74HC157: I0x = input A (bypass), I1x = input B (delayed), Zx = output Y. S LOW = A = bypass (R5 pulls S low when the Nano is off / in reset / unprogrammed), S HIGH = B = delayed replay. Channel 1 = RST2, 2 = FFA2, 3 = FFB2, 4 unused (inputs to GND).
C. PPQN jumper, mux pull-down, test points
PPQN (Nano D10/D11, internal pull-ups): JP1 both open = 96 (default, plain DX) JP1 1-2 closed (D10) = 48 JP1 3-4 closed (D11) = 24 (DXa/Stretch/MIDI slaved)
R5: MUX_SEL pull-down = bypass by default
Test points (scope): TP1 replay pulse, TP2 RST2 chip side, TP3 RST2 plug side, TP4 GND, TP5 clock
D. Arduino Nano (U2) on 2 x 1x15 female headers
D13 = LED_ACT: the Nano's own 'L' LED (no external part)
U2 +5V is the DX logic rail (via J1 DIP16). UNPLUG NANO BEFORE USB.
Series protection 1k (U1 outputs -> Nano inputs)
E. DX clock input (96 PPQN tick, rising edge)
J3 pin 1 -> DX CLOCK OUT node: R791 lead on the Q709-collector side (0/5 V, idles low, rising edge = tick). Clip-on grabber or tack solder. R6 10k series + R7 100k pull-down + C7 1nF -> two Schmitt inverters in series = non-inverting: rising edge at R791 = rising edge at D3.
Unused 74HC14 gates: inputs to GND, outputs open
F. SNARE DELAY pot, power, decoupling, mounting
J2 -> rear-panel 10k lin pot "SNARE DELAY 0 <-> 1 BEAT": 1 = CCW lug (GND), 2 = wiper, 3 = CW lug (+5V). R4 + C6 = RC filter into A0.
C1 bulk at J1; C2 at U1, C3 at U3, C4 at U4 pin 14, C5 at Nano pins 27/29
+5V and GND come from the DX through J1 (DIP16 / DIP8). No +-12V on this socket.

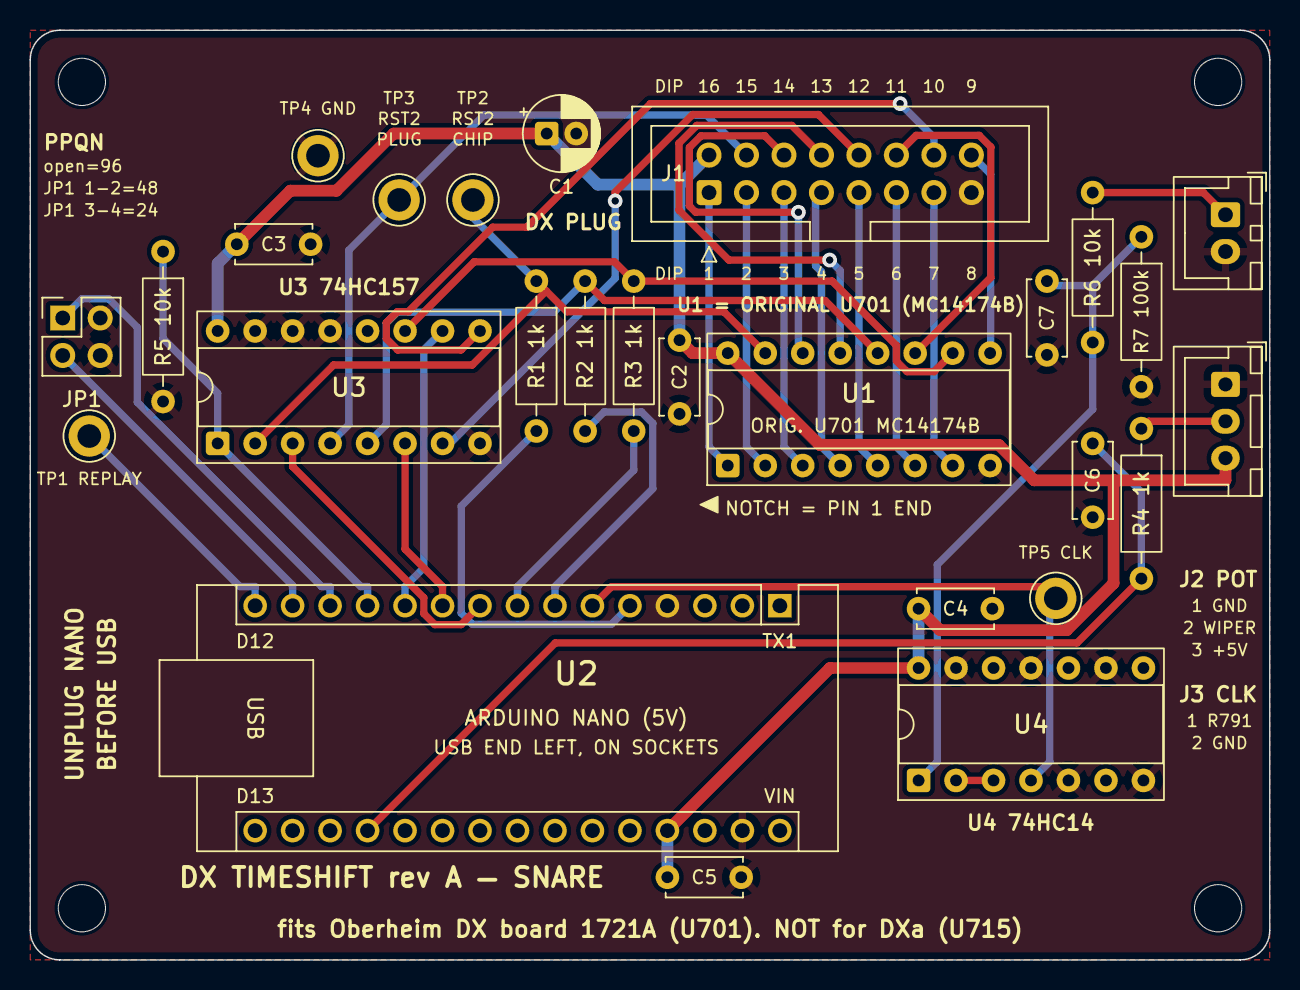
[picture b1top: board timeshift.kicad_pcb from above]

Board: 2 copper layers, 84.0 x 63.0 mm, 31 parts (0 on the bottom side), 35 nets.

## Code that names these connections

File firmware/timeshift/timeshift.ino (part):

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//  Pin map  (PROJECT_BRIEF.md §3.5, locked. Do not change without changing
//  the circuit board too.)
// ----------------------------------------------------------------------------
const uint8_t PIN_RST2_IN   = 2;   // INT0. From U701 pin 15. Rising edge = snare hit.
const uint8_t PIN_CLK_IN    = 3;   // INT1. DX clock via 74HC14. Rising edge = 1 tick.
const uint8_t PIN_FFA2_IN   = 4;   // From U701 pin 12. Level bit A.
const uint8_t PIN_FFB2_IN   = 5;   // From U701 pin 10. Level bit B.
const uint8_t PIN_RST2_OUT  = 6;   // Replayed trigger  -> 74HC157 input 1B.
const uint8_t PIN_FFA2_OUT  = 7;   // Replayed level A  -> 74HC157 input 2B.
const uint8_t PIN_FFB2_OUT  = 8;   // Replayed level B  -> 74HC157 input 3B.
const uint8_t PIN_MUX_SEL   = 9;   // 74HC157 S. LOW = bypass (stock), HIGH = delayed.
const uint8_t PIN_PPQN_JP1_12 = 10;  // JP1 position 1-2 (to GND). Fitted = 48 PPQN.
const uint8_t PIN_PPQN_JP1_34 = 11;  // JP1 position 3-4 (to GND). Fitted = 24 PPQN.
const uint8_t PIN_TP_REPLAY = 12;  // Test point TP1: high during each replayed trigger.
const uint8_t PIN_LED_ACT   = 13;  // On-board LED.
const uint8_t PIN_POT       = A0;  // Pot wiper (via 1 kΩ + 100 nF filter).

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// ----------------------------------------------------------------------------
static uint32_t halMicros()               { return micros(); }
static uint16_t halReadPot()              { return (uint16_t)analogRead(PIN_POT); }
static bool     halReadRst2In()           { return digitalRead(PIN_RST2_IN) == HIGH; }
static bool     halReadFfa2In()           { return digitalRead(PIN_FFA2_IN) == HIGH; }
static bool     halReadFfb2In()           { return digitalRead(PIN_FFB2_IN) == HIGH; }
static void     halWriteRst2Out(bool v)   { digitalWrite(PIN_RST2_OUT, v ? HIGH : LOW); }
static void     halWriteFfa2Out(bool v)   { digitalWrite(PIN_FFA2_OUT, v ? HIGH : LOW); }
static void     halWriteFfb2Out(bool v)   { digitalWrite(PIN_FFB2_OUT, v ? HIGH : LOW); }
static void     halWriteMuxSel(bool v)    { digitalWrite(PIN_MUX_SEL, v ? HIGH : LOW); }
static void     halWriteTestPoint(bool v) { digitalWrite(PIN_TP_REPLAY, v ? HIGH : LOW); }
static void     halWriteLed(bool v)       { digitalWrite(PIN_LED_ACT, v ? HIGH : LOW); }
static void     halDelayMicros(uint16_t us) { delayMicroseconds(us); }
// The main loop is the only caller, never an interrupt, so a plain
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  // Outputs: set LOW first, then make them outputs, so they never glitch high.
  // MUX_SEL LOW = BYPASS: the DX is stock until we decide otherwise. (The
  // 10 kΩ pull-down on the board already holds it LOW while we boot.)
  const uint8_t outputs[] = {PIN_RST2_OUT, PIN_FFA2_OUT, PIN_FFB2_OUT,
                             PIN_MUX_SEL, PIN_TP_REPLAY, PIN_LED_ACT};
  for (uint8_t i = 0; i < sizeof(outputs); i++) {
    digitalWrite(outputs[i], LOW);
    pinMode(outputs[i], OUTPUT);
  }

  // Inputs. The DX lines are driven by real logic outputs: no pull-ups.
  pinMode(PIN_RST2_IN, INPUT);
  pinMode(PIN_CLK_IN, INPUT);
  pinMode(PIN_FFA2_IN, INPUT);
  pinMode(PIN_FFB2_IN, INPUT);
  // PPQN jumper header JP1 (silkscreen "open=96, 1-2=48, 3-4=24"): a shunt
  // shorts the pin to GND; the internal pull-up makes an open position read
  // HIGH.
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  // Attach the interrupts last, when everything else is ready. Clear any
  // edge the hardware may have remembered while we were booting.
  EIFR = _BV(INTF0) | _BV(INTF1);
  attachInterrupt(digitalPinToInterrupt(PIN_RST2_IN), onSnareHit, RISING);
  attachInterrupt(digitalPinToInterrupt(PIN_CLK_IN), onClockTick, RISING);
}

// ----------------------------------------------------------------------------
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
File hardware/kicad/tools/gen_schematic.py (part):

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    r6a, _ = R6.pin(1)
    r6b, _ = R6.pin(2)
    S.wire(p1, r6a)
    S.label("CLK_TAP", p1, (1, 0))
    S.check(J3, 1, "CLK_TAP")
    S.check(R6, 1, "CLK_TAP")
    e = (p2[0] + G, p2[1])
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    S.wire(cnode, c7t)
    S.junction(node)
    S.junction(cnode)
    S.label("CLK_RC", cnode, (1, 0))
    S.term(R7, 2)
    S.term(C7, 2)
    for P, pin, net in ((R6, 2, "CLK_RC"), (R7, 1, "CLK_RC"), (C7, 1, "CLK_RC"), (R7, 2, "GND"), (C7, 2, "GND")):
        S.check(P, pin, net)
    U4A = S.place(C["U4"], 223.52, p1[1], unit=1, ref_at=(223.52, p1[1] - 5.08), val_at=(223.52, p1[1] + 5.08))
    ia, _ = U4A.pin(1)
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    ib, _ = U4B.pin(3)
    ob, _ = U4B.pin(4)
    S.wire(oa, ib)
    S.label("CLK_INV", oa, (1, 0))
    S.term(U4B, 4, "CLK_IN")
    S.check(U4A, 1, "CLK_RC")
    S.check(U4A, 2, "CLK_INV")
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    r4a, _ = R4.pin(1)
    r4b, _ = R4.pin(2)
    S.wire(w, r4a)
    S.label("POT_WIPER", w, (1, 0))
    S.check(J2, 2, "POT_WIPER")
    S.check(R4, 1, "POT_WIPER")
    welb = 327.66
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    S.term(C6, 2)
    lp = (cn[0] + 5.08, cn[1])
    S.wire(cn, lp)
    S.label("POT_W", lp, (1, 0))
    S.check(R4, 2, "POT_W")
    S.check(C6, 1, "POT_W")
    S.text("J2 -> rear-panel 10k lin pot \"SNARE DELAY 0 <-> 1 BEAT\":\n"
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
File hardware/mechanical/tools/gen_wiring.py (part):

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    HDR2DIP = dict(NL.HDR2DIP)
    U701_FUNC = dict(NL.U701_FUNC)
    U3PINS = NL.BY_REF["U3"]["pins"]
    PLUG_TO_U3 = {15: [p for p, n in U3PINS.items() if n == "RST2_PLUG"][0],
                  12: [p for p, n in U3PINS.items() if n == "FFA2_PLUG"][0],
                  10: [p for p, n in U3PINS.items() if n == "FFB2_PLUG"][0]}
    SOURCE = "hardware/kicad/tools/netlist.py"
except Exception:  # pragma: no cover - fallback copy of PROJECT_BRIEF.md 3.5
    HDR2DIP = {1: 1, 2: 16, 3: 2, 4: 15, 5: 3, 6: 14, 7: 4, 8: 13,
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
